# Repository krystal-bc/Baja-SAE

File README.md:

# Baja-SAE
Program for taking measurements and data logging on a Baja SAE vehicle. Property of CSULA Baja SAE 2017-2018.

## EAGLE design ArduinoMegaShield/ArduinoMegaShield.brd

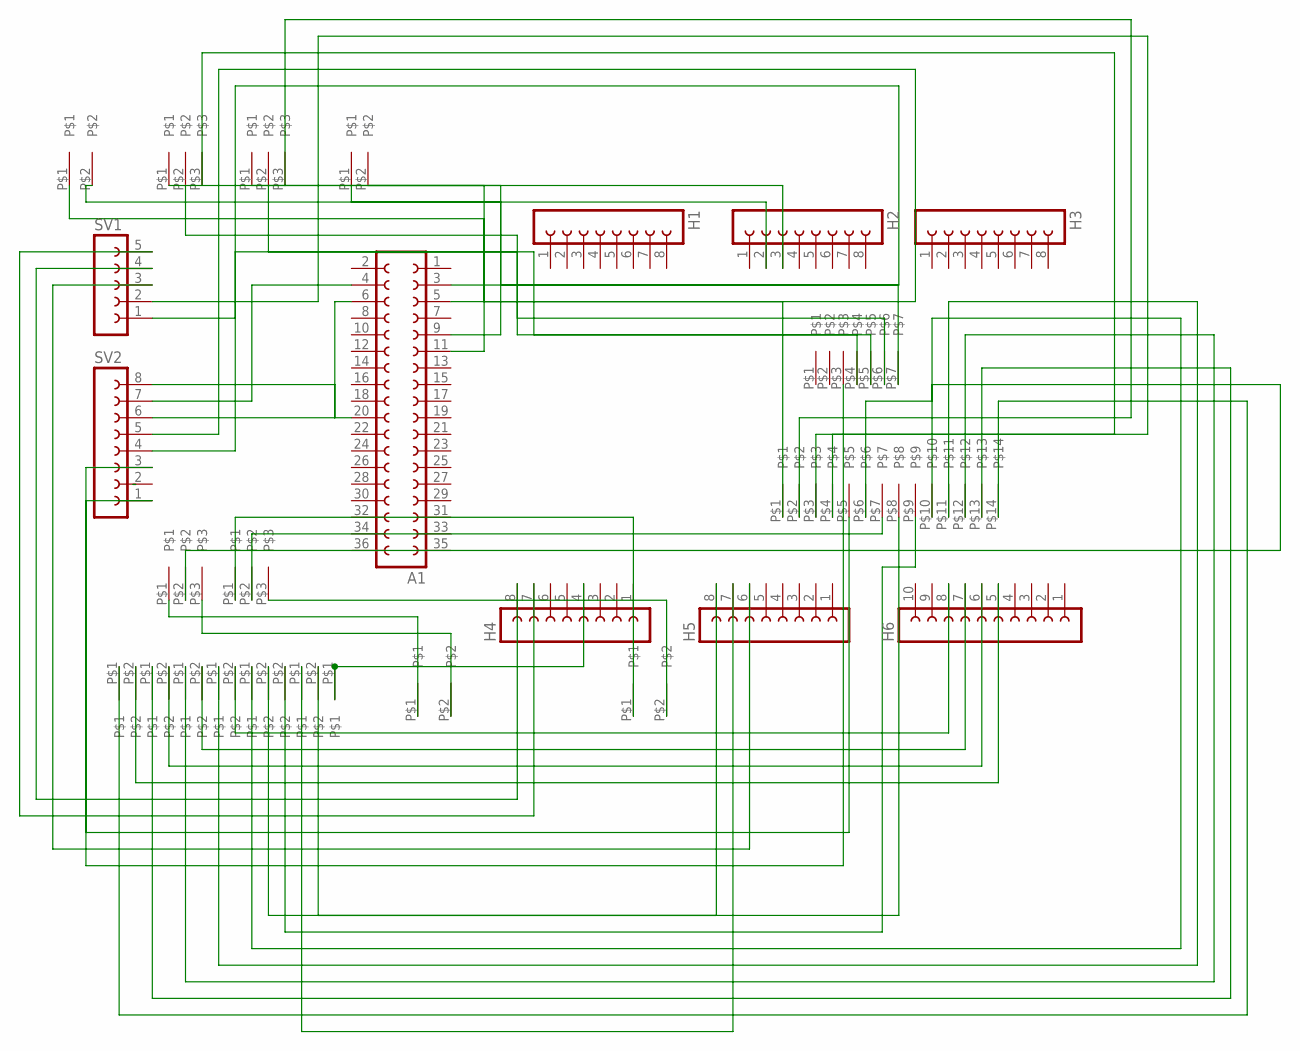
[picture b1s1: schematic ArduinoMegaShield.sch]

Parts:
A1: FE18-2
H1, H2, H3, H4, H5: FE08-1; FE08
H6: FE10-1; FE10
SV1: FE05-1
SV2: FE08-1; FE08
U$1: DEVICE; PACKAGE
U$2, U$4, U$5, U$6: DEV; PAC
U$3, U$13, U$15: 2PIN2.54
U$7: BATTERY
U$8, U$9, U$10, U$11, U$12: DEV2; PAC2
U$14: UPDATED9PIN
U$16, U$17: 10KRESISTOR

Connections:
GND: U$7.P$1, U$14.P$1
unnamed: H2.3, U$3.P$2
unnamed: H2.2, U$3.P$1
unnamed: U$1.P$7, U$7.P$2
unnamed: U$5.P$1, U$16.P$1
unnamed: U$1.P$6, U$2.P$2
unnamed: U$1.P$5, U$4.P$2
unnamed: U$4.P$3, U$14.P$2
unnamed: U$2.P$3, U$14.P$3
unnamed: H4.7, SV1.5
unnamed: H4.8, SV1.4
unnamed: H5.6, SV1.3
unnamed: SV1.2, U$14.P$4
unnamed: SV1.1, U$1.P$4
unnamed: A1.20, SV2.8
unnamed: A1.4, SV2.7
unnamed: A1.6, SV2.6
unnamed: A1.5, SV2.5
unnamed: A1.3, SV2.4
unnamed: SV2.3, U$14.P$5
unnamed: SV2.1, U$1.P$3
unnamed: A1.9, U$4.P$1
unnamed: A1.11, U$2.P$1
unnamed: H6.5, U$8.P$2
unnamed: H6.6, U$9.P$2
unnamed: H6.7, U$10.P$2
unnamed: H6.8, U$11.P$2
unnamed: H5.8, U$12.P$2
unnamed: H5.7, U$13.P$1
unnamed: H4.4, U$15.P$1
unnamed: U$5.P$3, U$16.P$2
unnamed: U$5.P$2, U$14.P$6
unnamed: U$6.P$2, U$14.P$7
unnamed: U$6.P$1, U$17.P$1
unnamed: U$14.P$8, U$15.P$2
unnamed: U$6.P$3, U$17.P$2
unnamed: U$13.P$2, U$14.P$9
unnamed: U$12.P$1, U$14.P$10
unnamed: U$11.P$1, U$14.P$11
unnamed: U$10.P$1, U$14.P$12
unnamed: U$9.P$1, U$14.P$13
unnamed: U$8.P$1, U$14.P$14

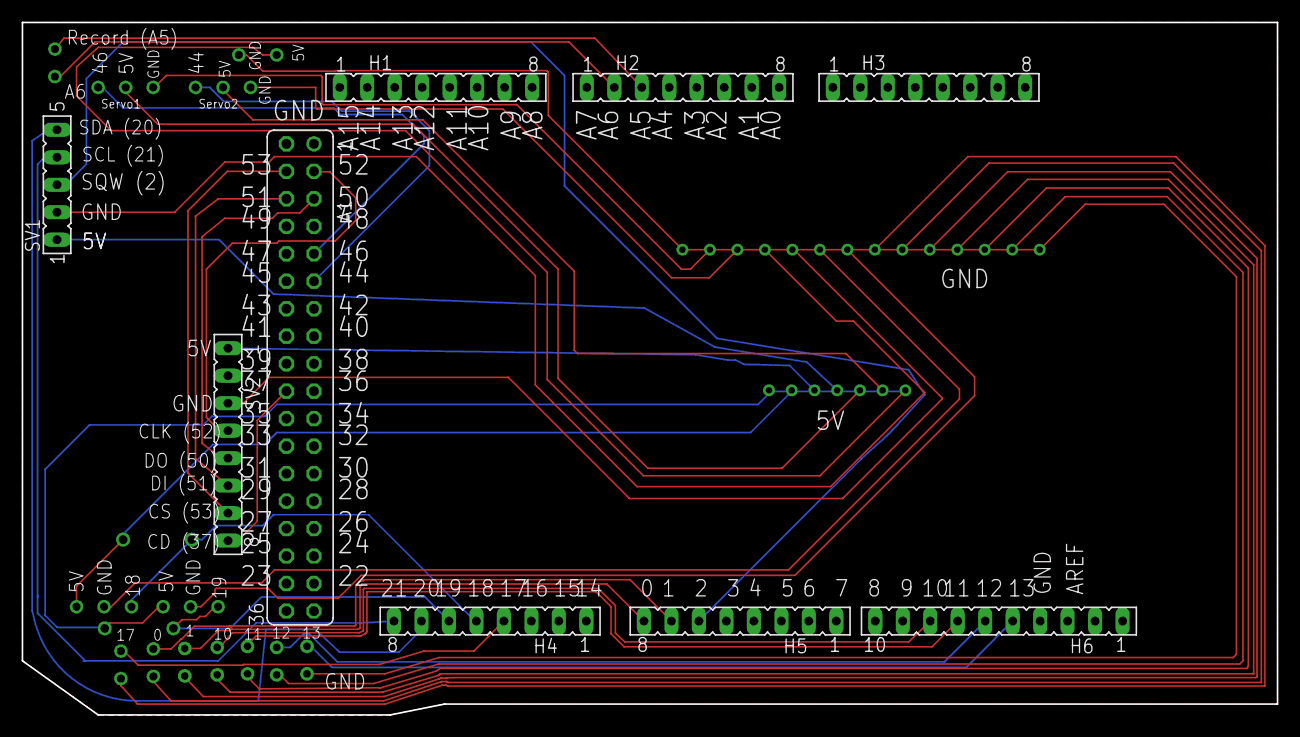
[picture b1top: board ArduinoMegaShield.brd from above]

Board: 2 copper layers, 116.0 x 64.0 mm, 26 parts (0 on the bottom side), 42 nets.

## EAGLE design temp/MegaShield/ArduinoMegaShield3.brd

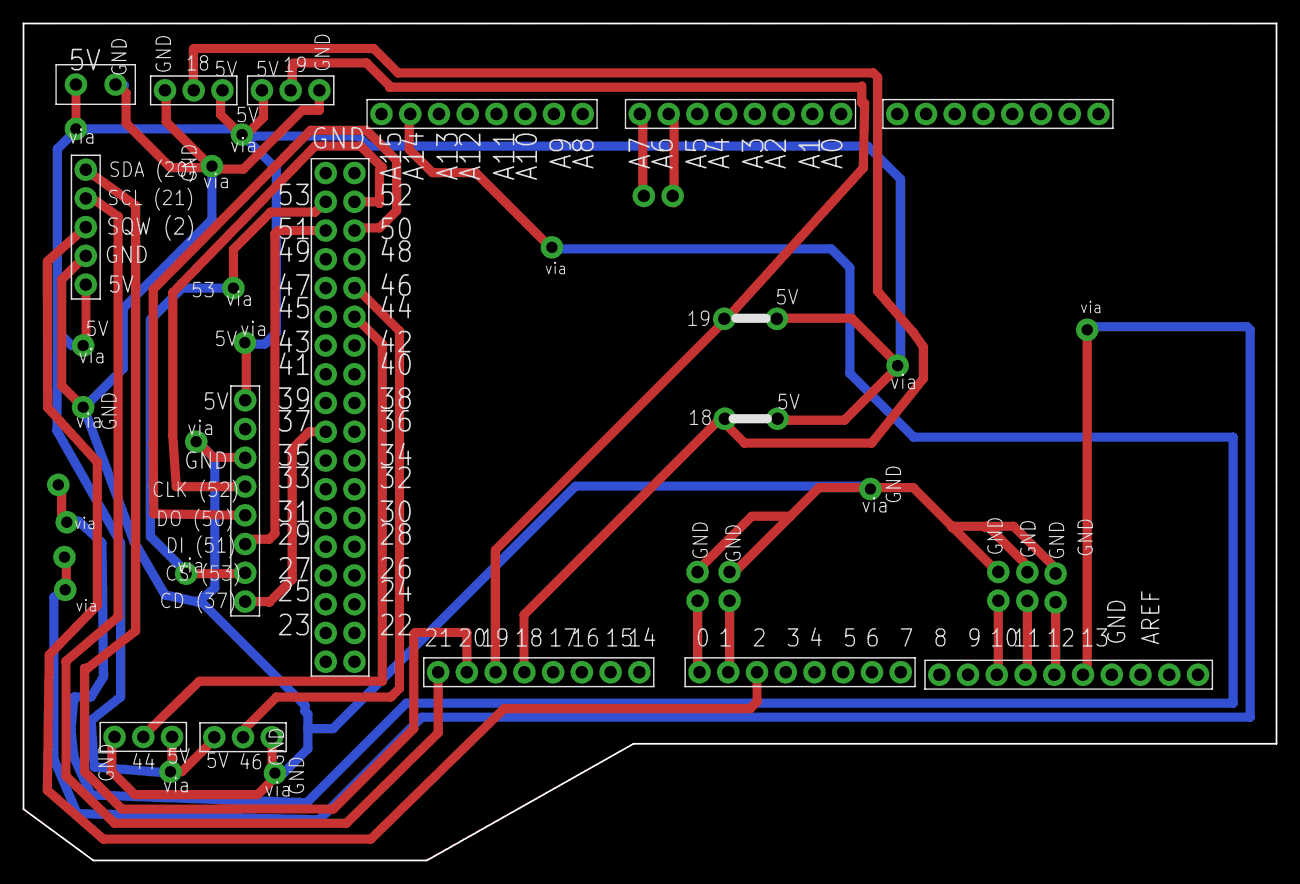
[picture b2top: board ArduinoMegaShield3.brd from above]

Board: 2 copper layers, 110.7 x 74.0 mm, 22 parts (0 on the bottom side), 17 nets.

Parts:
U$1, U$2, U$3, U$4, U$5: 8PINHEADER2.54MM
U$6: 10PINHEADER2.54MM
U$7: 18X2HEADER2.54MM
U$8: 5PINHEADER2.54MM
U$9, U$11: SERVOS
U$10: SDCARDMODULE
U$12, U$13: HALLEFFECTSENSORS
U$14, U$15, U$17, U$18, U$19: 2PIN2.54MM
U$20, U$21: 2PIN11MM
U$22: BUTTONS
U$23: 2PINTERMINAL3.5MM

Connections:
GND: U$8.GND, U$10.GND, U$14.GND, U$15.GND, U$17.GND, U$18.GND, U$19.GND, U$23.GND
unnamed: U$4.P$7, U$22.P$1
unnamed: U$4.P$6, U$22.P$2
unnamed: U$2.P$2, U$8.P$1
unnamed: U$2.P$1, U$8.P$2
unnamed: U$1.P$3, U$8.P$3
unnamed: U$7.P$20, U$10.P$5
unnamed: U$7.P$21, U$10.P$4
unnamed: U$7.P$16, U$10.P$3
unnamed: U$7.P$17, U$10.P$2
unnamed: U$7.P$9, U$10.P$1
unnamed: U$1.P$2, U$14.P$1
unnamed: U$1.P$1, U$15.P$1
unnamed: U$6.P$1, U$17.P$1
unnamed: U$6.P$2, U$18.P$1
unnamed: U$6.P$3, U$19.P$1
TOP: U$10.5V, U$20.5V, U$21.5V, U$23.5V

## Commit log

2017-09-15 Add files via upload
    Final-ish code. Still waiting on Real Time Clock module to come in the mail in order to add it into the wiring/code.
2017-09-16 Rename strainTestFinal.ino to BajaFinal.ino
2017-10-14 Add files via upload
    Incomplete button integration
2017-10-15 Button Integration Complete
2017-10-15 Add Load Cell Test
2017-10-15 Preliminary Hall Effect sensor code added
2017-10-19 Updated Shield files
2017-10-25 Update part numbers
2017-11-10 Update Bill of Materials
    Battery research
2017-11-10 Add battery folder
    Datasheets for batteries, voltage sensor and BMS, voltage sensor
2017-11-11 Add servo test
2017-11-11 Add button test
2017-11-12 remove Serial prints
2017-12-13 update pinouts, add SD writes
2017-12-13 update pinouts and SD writes
2017-12-13 update SD header, streamline load cell code
2017-12-15 update writes to SD card
2018-01-04 add transistor datasheet
2018-01-04 Dash Latch Parts
2018-01-10 integrate hall effect sensors
2018-01-10 hall effect sensor code updated for modularity
2018-01-17 Add files via upload
    Keep this To-Do List updated and check back regularly.
2018-01-18 rename and update to-do list
2018-01-18 add transistor test
2018-01-19 update 1/18/18
2018-01-25 update button for analog pin
2018-01-25 add fan battery drain
2018-01-26 update RTC_SD_Test
2018-01-26 fan battery drain code adjusted
2018-01-26 integrated updates to SD and analog button
2018-01-26 integrate changes to button and SD card
    for Baja final serial: edits from test code version back to final version
2018-01-26 Just changed serial print statements
2018-01-26 changed temperature sensor readings
2018-01-26 temp sensor values corrected + fan turns off at a threshold
2018-01-27 update BajaFinal to match BajaFinalSerial
    minor updates to BajaFinalSerial
2018-02-09 adjustment for bad LEDs
2018-02-09 update for functioning LEDs, display mph & ratio
2018-02-23 update hall effect code, pinouts
2018-03-19 Datasheet and Arduino library
2018-03-19 add .ino file
    doesn't recognize the default degrees per second range (line 34)
2018-03-21 Accelerometer and gyro
2018-03-28 Create SDInterface
2018-03-29 replace I2C sample with SPI, added two accl SPI
2018-04-20 file updates
2018-06-29 Add files via upload
    header needs to be updated, picture resizing issue, logos need text. add header before logo that says "Follow Us!" or something. See if it's possible to add facebook/insta widget
2018-07-04 Add .gitignore
2018-07-04 Adding test images to test carousel Adding height and width to carousel images Modifying social media icons using Font Awesome library
2018-07-04 Moving Homepage.html to Homepage/Homepage.html
2018-07-04 Moving carousel test images Modifying HomePage.html to match new test images' paths
2018-07-04 Modifying HomePage.html in accordance to new test images' paths for carousel testing
2018-07-04 Attempting to remove duplicate directories
2018-07-04 Fixing redundant directories
2018-10-31 change datatypes, add time, clean
    changed long to float for more accurate inch measurements. removed use of centimeter conversions. added microseconds elapsed. updated pins.
2018-11-15 SD card code integrated
2018-11-15 integrate SD card code
2018-12-31 Adding hall.py
2019-01-01 hall.py can now record revolutions per second and write into he_results.csv with time stamps and RPS (Revolutions Per Second)
2019-01-01 Adding correct time frame recordation along with generating NEW `.csv` files names of when the data was recorded
2019-01-01 Adding comment to `.gitignore` Vim files
2020-07-08 for Liz
